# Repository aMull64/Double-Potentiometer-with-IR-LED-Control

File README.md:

## Problem Formulation
  This project is an extension of a pre-existing product, that being a Logitech Z313 Speaker System with Subwoofer [1]. This speaker system is wired as the output to a Sony TV, one that can be controlled with a wireless controller, but does not respond to volume up or volume down. This is okay because the Logitech speakers do not work with the TV volume. The Logitech speakers control their volume by manually controlling a potentiometer. I would like the ability to control the volume remotely. The TV remote not controlling the TV volume works with us in this case; we can read the IR signals coming from the remote with an IR sensor and adjust the potentiometers to control the volume.
  
  The pre-existing circuit can be seen in Circuit_Board_Scale, and the wires we will be working with can be seen in Circuit_Board_Connectors.

The pins go as follows: GND, Lout, Rout, GND, Lin, Rin, OUT, IN, LED. Looking at the back reveals that both grounds are connected to each other, creating a common ground.
- Lout and Rout are the left and right channels post-potentiometer
- Lin and Rin are the left and right channels pre-potentiometer
- OUT and IN seem to be used as a way to tell if the system is on or off. They are connected through the dbdt switch and nothing else.
- LED is the power that goes to the LED; we might be able to tap into this power for the integrated circuits. 12V

## Proposed Solution
  In order to read IR signals, we need to include a microcontroller, but in order to choose one, we need to know what else is needed. 2 physical buttons will take the place of the current physical potentiometer, which changes the internal volume variable. And an RGB LED to determine when the system is powered, this can also be used as a debugging tool, changing colors when changing internal variables. 2 digital potentiometers are used to adjust the left and right channel, controlled through I2C. A DBDT switch will be used to control the "power" LED signifier, connect the standby OUT and IN, and introduce power to the rest of the system. The microcontroller in question will need 2 pins for I2C communication (and the ability to do that), 2 pins for manual control (2 buttons), 2 pins for the LED (Blue and Green), and 1 pin for the IR Sensor. In total, we need 7 usable pins, and the ATtiny 404 will fit our case [2]. We will include 2 digital potentiometers that are controlled with I2C 

##  Version 1:
  The first iteration was successful in communicating with the digital potentiometers through I2C. The programming for the experimental stage gave complete control to the RBG LED, the 2 Digital Potentiometers, the ability to read the IR signals from the remote, and the ability to compile the program within the 4kB flash memory limit. This came with the problem of not reading enough datasheets. After further examination of the digital potentiometer datasheet, it does not appreciate negative voltage through the two terminals (which audio covers a range of about [-2.5, 2.5]). This led to some complications and created a design that fundamentally did not work.

##  Version 2:
  The issue was tackled by using a coupling capacitor within a voltage divider to shift the range into a completely positive voltage [0, 5]. The side buttons were removed because they were virtually inaccessible when the casing was completely put on. A different voltage regulator was used that established a 5V rail, which is how the voltage divider was allowed to work.

## References
[1] https://www.logitech.com/en-us/shop/p/z313-speaker-system-subwoofer.980-000382 

[2] https://www.digikey.com/en/products/detail/microchip-technology/ATTINY404-SSNR/8594960

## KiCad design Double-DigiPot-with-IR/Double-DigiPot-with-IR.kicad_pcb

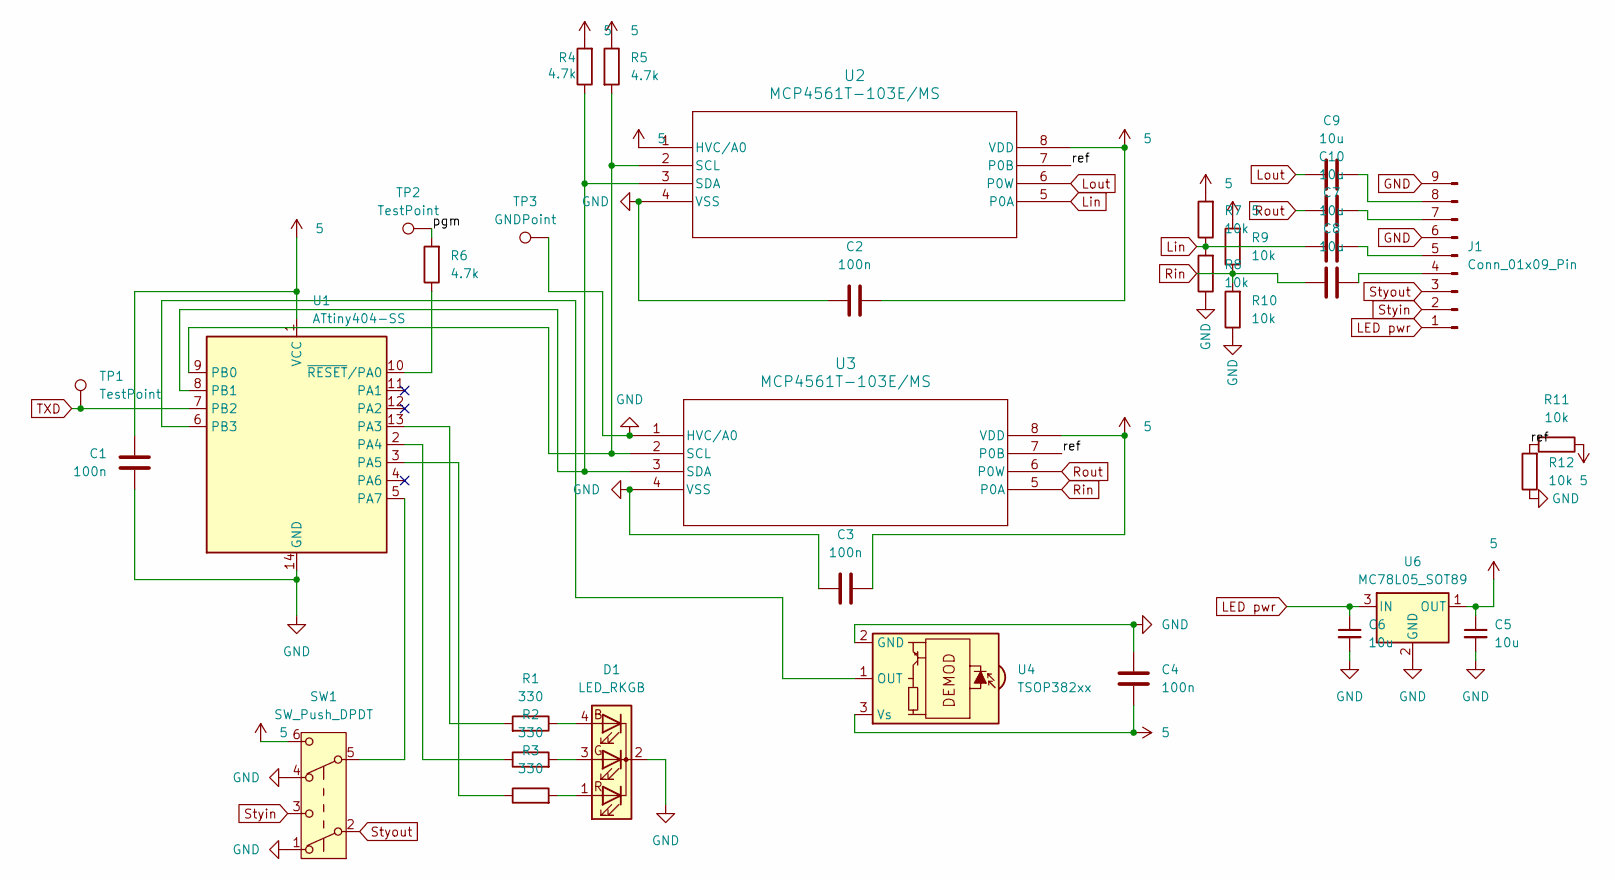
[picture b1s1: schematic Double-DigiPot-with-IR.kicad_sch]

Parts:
C1, C2, C3, C4: 100n; C_0805_2012Metric_Pad1.18x1.45mm_HandSolder
C5, C6, C7, C8, C9, C10: 10u; C_0805_2012Metric_Pad1.18x1.45mm_HandSolder
D1: LED_RKGB; LED_D5.0mm-4_RGB_Staggered_Pins
J1: Conn_01x09_Pin; PinSocket_1x09_P2.54mm_Vertical
R1, R2, R3: 330; R_0805_2012Metric_Pad1.20x1.40mm_HandSolder
R4, R5, R6: 4.7k; R_0805_2012Metric_Pad1.20x1.40mm_HandSolder
R7, R8, R9, R10, R11, R12: 10k; R_0805_2012Metric_Pad1.20x1.40mm_HandSolder
SW1: SW_Push_DPDT; CONN_S2273_APM
TP1, TP2: TestPoint; TestPoint_Pad_D4.0mm
TP3: GNDPoint; TestPoint_Pad_D4.0mm
U1: ATtiny404-SS; SOIC-14_3.9x8.7mm_P1.27mm
U2, U3: MCP4561T-103E/MS; MSOP8_MC_MCH
U4: TSOP382xx; Vishay_MINICAST-3Pin
U6: MC78L05_SOT89; SOT-89-3_Handsoldering

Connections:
5: C1.1, C2.2, C3.2, C4.1, C5.1, R4.2, R5.1, R7.2, R9.2, R11.1, SW1.6 (C), U1.1 (VCC), U2.1 (HVC/A0), U2.8 (VDD), U3.8 (VDD), U4.3 (Vs), U6.1 (OUT)
/pgm: R6.2, TP2.1 (1_1)
/ref: R11.2, R12.2, U2.7 (P0B), U3.7 (P0B)
GND: C1.2, C2.1, C3.1, C4.2, C5.2, C6.2, D1.2 (K), J1.6, J1.9, R8.1, R10.1, R12.1, SW1.1 (A), SW1.4 (A), TP3.1 (1_1), U1.14 (GND), U2.4 (VSS), U3.1 (HVC/A0), U3.4 (VSS), U4.2 (GND), U6.2 (GND)
LED pwr: C6.1, J1.1, U6.3 (IN)
Lin: C7.1, R7.1, R8.2, U2.5 (P0A)
Lout: C9.1, U2.6 (P0W)
unnamed: D1.4 (BA), R1.1
unnamed: D1.3 (GA), R2.2
unnamed: D1.1 (RA), R3.2
unnamed: C8.2, J1.4
unnamed: C7.2, J1.5
unnamed: C10.2, J1.7
unnamed: C9.2, J1.8
unnamed: R1.2, U1.13 (PA3)
unnamed: R2.1, U1.2 (PA4)
unnamed: R3.1, U1.3 (PA5)
unnamed: SW1.5 (B), U1.5 (PA7)
unnamed: R5.2, U1.9 (PB0), U2.2 (SCL), U3.2 (SCL)
unnamed: R4.1, U1.8 (PB1), U2.3 (SDA), U3.3 (SDA)
unnamed: U1.6 (PB3), U4.1 (OUT)
unnamed: R6.1, U1.10 (~RESET/PA0)
Rin: C8.1, R9.1, R10.2, U3.5 (P0A)
Rout: C10.1, U3.6 (P0W)
Styin: J1.2, SW1.3 (C)
Styout: J1.3, SW1.2 (B)
TXD: TP1.1 (1_1), U1.7 (PB2)

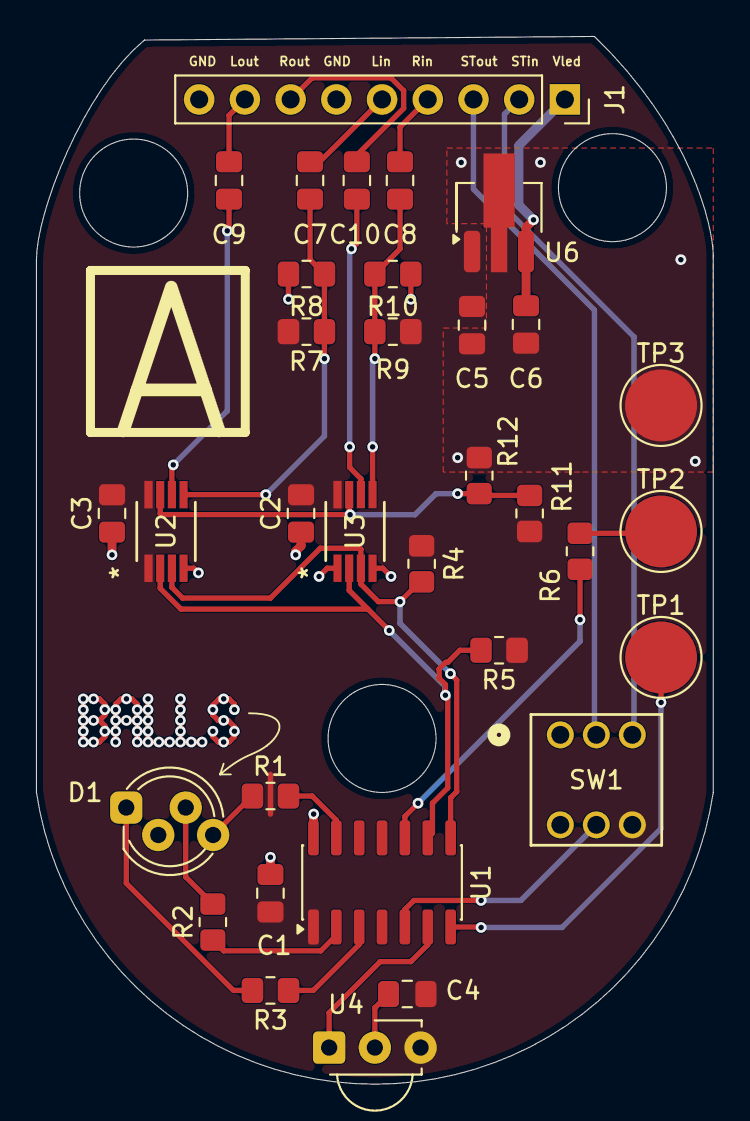
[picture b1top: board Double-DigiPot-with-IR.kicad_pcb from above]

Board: 2 copper layers, 37.6 x 58.2 mm, 33 parts (0 on the bottom side), 27 nets.

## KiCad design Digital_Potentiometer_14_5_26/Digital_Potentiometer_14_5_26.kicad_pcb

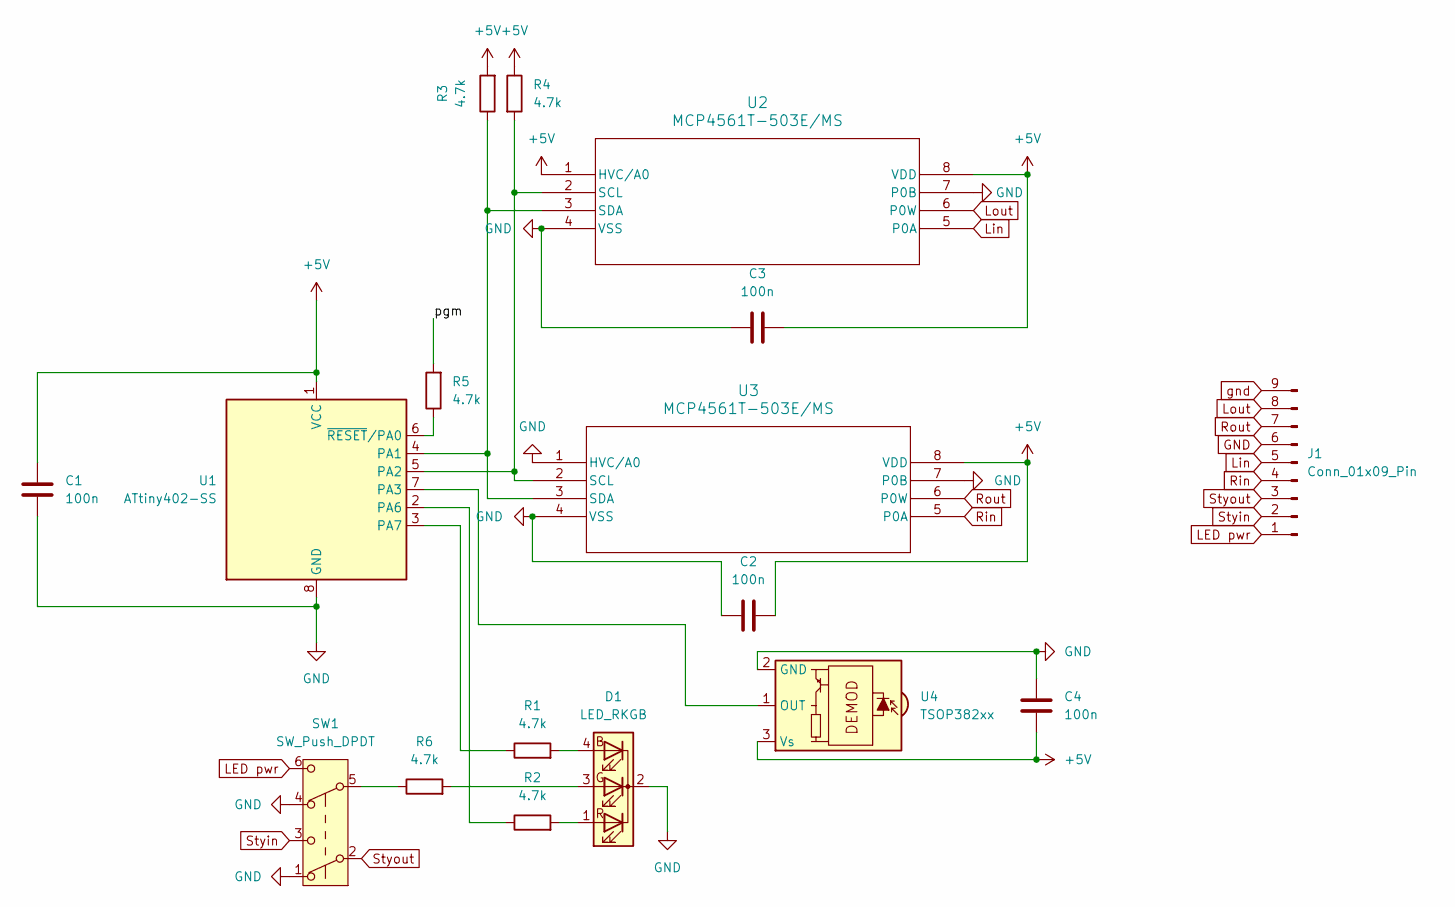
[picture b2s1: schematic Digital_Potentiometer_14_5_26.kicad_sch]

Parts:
C1, C2, C3, C4: 100n; C_0805_2012Metric
D1: LED_RKGB; LED_D5.0mm-4_RGB_Staggered_Pins
J1: Conn_01x09_Pin; Molex_Pico-Clasp_202396-0907_1x09-1MP_P1.00mm_Horizontal
R1, R3, R5, R6: 4.7k; R_0805_2012Metric
R2, R4: 4.7k; C_0805_2012Metric
SW1: SW_Push_DPDT; CONN_S2273_APM
U1: ATtiny402-SS; SOIC-8_3.9x4.9mm_P1.27mm
U2, U3: MCP4561T-503E/MS; MSOP8_MC_MCH-M
U4: TSOP382xx; Vishay_MINICAST-3Pin

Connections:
+5V: C1.1, C2.2, C3.2, C4.1, R3.2, R4.1, U1.1 (VCC), U2.1 (HVC/A0), U2.8 (VDD), U3.8 (VDD), U4.3 (Vs)
/pgm: R5.2
GND: C1.2, C2.1, C3.1, C4.2, D1.2 (K), J1.6, SW1.1 (A), SW1.4 (A), U1.8 (GND), U2.4 (VSS), U2.7 (P0B), U3.1 (HVC/A0), U3.4 (VSS), U3.7 (P0B), U4.2 (GND)
LED pwr: J1.1, SW1.6 (C)
Lin: J1.5, U2.5 (P0A)
Lout: J1.8, U2.6 (P0W)
unnamed: D1.4 (BA), R1.2
unnamed: D1.3 (GA), R6.2
unnamed: D1.1 (RA), R2.2
unnamed: R6.1, SW1.5 (B)
unnamed: R3.1, U1.4 (PA1), U2.3 (SDA), U3.3 (SDA)
unnamed: R4.2, U1.5 (PA2), U2.2 (SCL), U3.2 (SCL)
unnamed: U1.7 (PA3), U4.1 (OUT)
unnamed: R2.1, U1.2 (PA6)
unnamed: R1.1, U1.3 (PA7)
unnamed: R5.1, U1.6 (~RESET/PA0)
Rin: J1.4, U3.5 (P0A)
Rout: J1.7, U3.6 (P0W)
Styin: J1.2, SW1.3 (C)
Styout: J1.3, SW1.2 (B)
gnd: J1.9

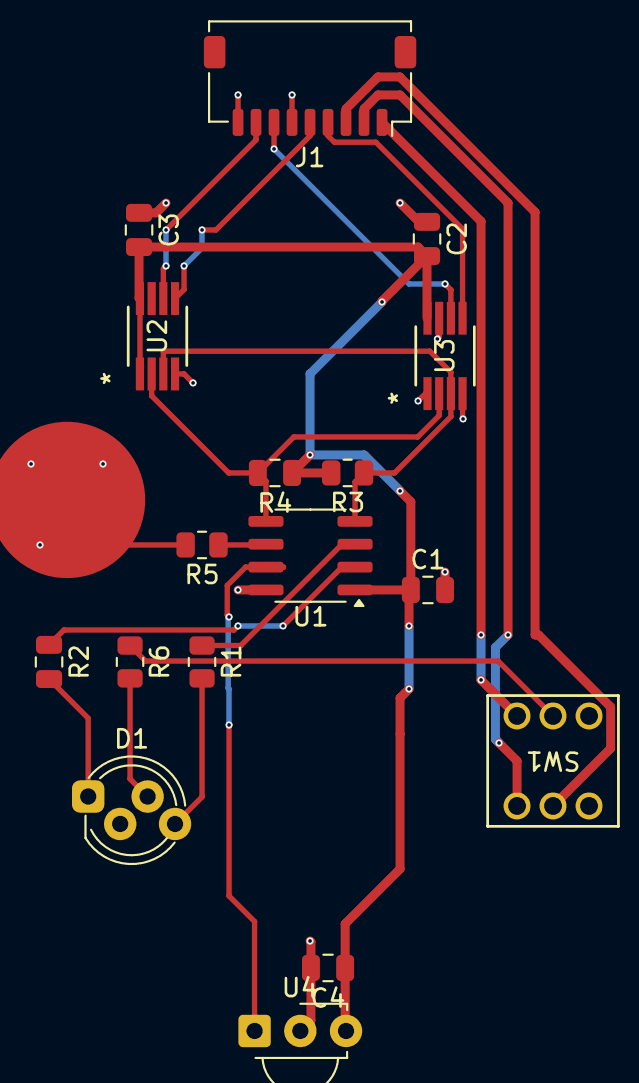
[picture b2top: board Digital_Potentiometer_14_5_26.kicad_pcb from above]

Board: 2 copper layers, 17 parts (0 on the bottom side), 19 nets.

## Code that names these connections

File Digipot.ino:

#include <Wire.h>
#include <avr/io.h>
#include <avr/interrupt.h>

//#define DEBUG

#define POWER_STATUS_PIN (8)
#define RED_LED_PIN (2)
#define BLUE_LED_PIN (3)
#define SENSOR_PIN (4)

#define RED_LED_bm (PIN4_bm)
#define BLUE_LED_bm (PIN5_bm)

#define SENSOR_bm (PIN3_bm)
#define SENSOR_pos (3)

#define MIN_SAMPLES_0 (1)
#define MIN_SAMPLES_1 (5)
#define MAX_SAMPLES_0 (4)
#define MAX_SAMPLES_1 (8)
#define MIN_SAMPLES_START (9)
#define MAX_SAMPLES_START (50)

#define NUM_BITS (12)

#define VOL_UP_CMD (0x490)
#define VOL_DOWN_CMD (0xC90)
#define VOL_MUTE (0x290)
#define IR_DOWNTIME (500)

#define LED_ON_TICKS (1000)
#define MAX_COMBO (30)

volatile uint8_t vol = 1;
volatile uint8_t mute_flag = 0;
volatile uint8_t sent_vol = 0;

// Your register address, which can be found on your IC's datasheet
#define SUB_0_ADDR 0x2E //please correct me if wrong, datasheet says '0101 11'b + A0 = 0010 111 (0 or 1)
#define SUB_1_ADDR 0x2F
#define WRITE_CMD 0x00

/*Pinouts:
(11)PA0 = programming Pin
(8)PA1 = Power Data Input
(0)PA4 = LED Red
(1)PA5 = LED Blue
(2)PA6 = Volume Up Pushbutton
(3)PA7 = Volume Down Pushbutton

(7)PB0 = SCL
(6)PB1 = SDA
(5)PB2 = TestPoint
(4)PB3 = IRLED
*/

ISR(TCA0_OVF_vect) {
    static volatile uint8_t samp_count = 0;
    static volatile uint8_t bit_count = 0;
    static volatile uint16_t cmd_buffer = 0x00;

    static volatile uint16_t red_led_on_ticks = 0;
    static volatile uint16_t blue_led_on_ticks = 0;

    static volatile uint16_t on_ticks = 0;
    static volatile uint8_t combo_meter = 0;

    static volatile uint16_t last_cmd = 0;

    uint8_t sensor_state = (PORTB.IN & SENSOR_bm) >> SENSOR_pos;

    if (sensor_state) {
      // Check to see if we just got high
      if(on_ticks <= IR_DOWNTIME){
        ++on_ticks;
        if(on_ticks == IR_DOWNTIME){
          combo_meter = 0;
        }
      }

      if (samp_count) {
        if (bit_count <= NUM_BITS)
          ++bit_count;

        if (samp_count > MIN_SAMPLES_0 && samp_count <= MAX_SAMPLES_0) {
          // I guess we do nothing
        }
        else if (samp_count > MIN_SAMPLES_1 && samp_count <= MAX_SAMPLES_1) {
          cmd_buffer |= (1 << (NUM_BITS - bit_count));
        }
        else if(samp_count > MIN_SAMPLES_START && samp_count <= MAX_SAMPLES_START) {
          // We got a start bit
          cmd_buffer = 0x00;
          bit_count = 0;
        }

        // Check how many bits we got
        if (bit_count == NUM_BITS) {
          if (last_cmd == cmd_buffer) {
            if (combo_meter < MAX_COMBO)
              ++combo_meter;
          }

          else {
            combo_meter = 0;
          }

          last_cmd = cmd_buffer;

          if (cmd_buffer == VOL_UP_CMD && vol < 255) {
            mute_flag = 0;

            if (combo_meter == MAX_COMBO) {
              vol = vol < 250 ? vol + 5 : 255;
            } else ++vol;

            red_led_on_ticks = LED_ON_TICKS;
          }

          else if (cmd_buffer == VOL_DOWN_CMD && vol > 0) {
            mute_flag = 0;

            if (combo_meter == MAX_COMBO) {
              vol = vol > 5 ? vol - 5 : 0;
            } else --vol;

            blue_led_on_ticks = LED_ON_TICKS;
          }

          else if (cmd_buffer == VOL_MUTE) {
            if (combo_meter == 1) {
              mute_flag = !mute_flag;
            }
          }
            
#ifdef DEBUG
          Serial.print("Command: 0x");
          Serial.print(cmd_buffer, HEX);
          Serial.print(" Volume: ");
          Serial.println(vol);
#endif
        }
      }

      if (red_led_on_ticks) {
        --red_led_on_ticks;
        PORTA.OUTSET = RED_LED_bm;
      } else if (mute_flag) {
        PORTA.OUTSET = RED_LED_bm;
      }
      else {
        PORTA.OUTCLR = RED_LED_bm;
      }
      
      if (blue_led_on_ticks) {
        --blue_led_on_ticks;
        PORTA.OUTSET = BLUE_LED_bm;
      } else {
        PORTA.OUTCLR = BLUE_LED_bm;
      }

      // Clear this for future samples
      samp_count = 0;
    }

    else {
      on_ticks = 0;
      ++samp_count; // It's faster this way trust me
    }
    
    // Clear the overflow interrupt flag to allow the next interrupt
    TCA0.SINGLE.INTFLAGS = TCA_SINGLE_OVF_bm;
}

void timer_init() {
  TCA0.SINGLE.PER = 250; // Hopefully 200us?
  TCA0.SINGLE.CTRLA = TCA_SINGLE_CLKSEL_DIV16_gc | TCA_SINGLE_ENABLE_bm;
  TCA0.SINGLE.INTCTRL = TCA_SINGLE_OVF_bm;
  sei();
}

void setup() {
	Wire.begin();
  Serial.begin(115200);

  pinMode(SENSOR_PIN, INPUT);
  pinMode(POWER_STATUS_PIN, INPUT);
  pinMode(RED_LED_PIN, OUTPUT);
  pinMode(BLUE_LED_PIN, OUTPUT);
  timer_init();
  
  Serial.println("Sony IR volume control with I2C digipot");
  Serial.print("CPU Frequency: ");
  Serial.print(F_CPU);
}

void loop() {

  uint8_t next_vol = mute_flag ?   0 : vol;
  if(next_vol != sent_vol){
    sent_vol = next_vol;
  
    // Write volume data
    Wire.beginTransmission(SUB_0_ADDR);  
    Wire.write(WRITE_CMD); 
    Wire.write(sent_vol);
    Wire.endTransmission();  

    Wire.beginTransmission(SUB_1_ADDR);  
    Wire.write(WRITE_CMD); 
    Wire.write(sent_vol);
    Wire.endTransmission();  

    Serial.print(" Volume: ");
    Serial.print(sent_vol);
    Serial.print(", Mute Flag: ");
    Serial.println(mute_flag);

  }
  
  delay(10);
}

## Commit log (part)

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2026-05-14 2 pictures of the circuit for scale and clarity
2026-05-14 Rename Cuircuit_Board_Scale.jpeg to Circuit_Board_Scale.jpeg
2026-05-31 Updated PCB
